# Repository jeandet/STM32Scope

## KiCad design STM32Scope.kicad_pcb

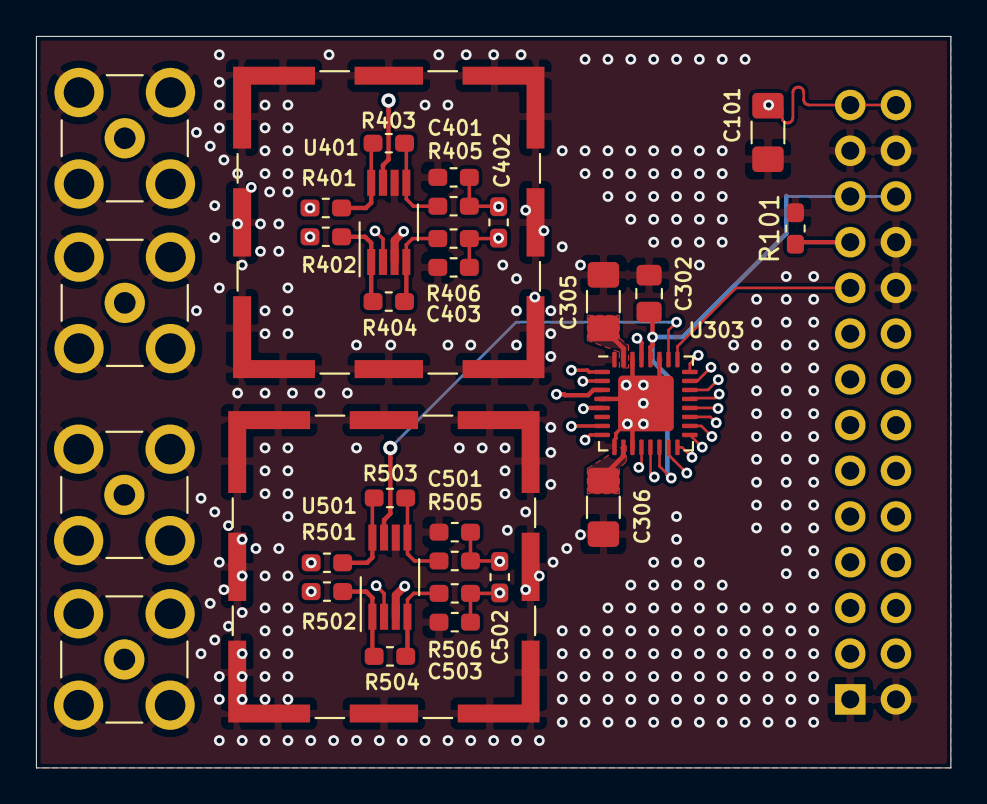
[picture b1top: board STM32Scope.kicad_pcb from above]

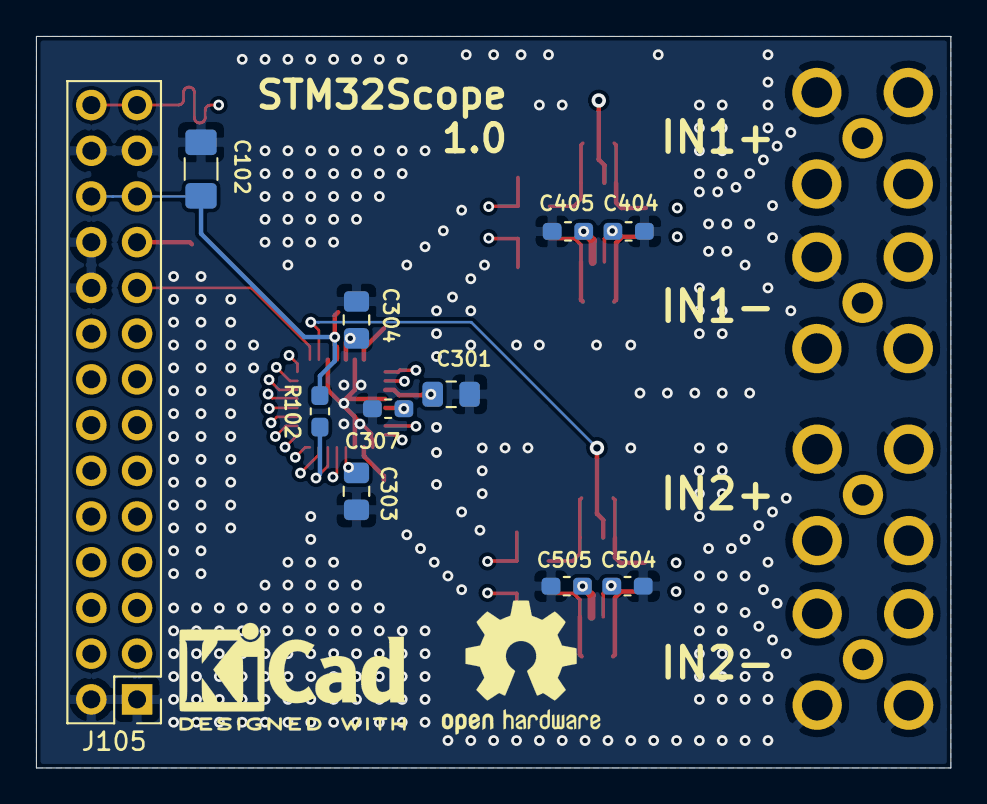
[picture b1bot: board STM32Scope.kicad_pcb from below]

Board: 4 copper layers, 50.8 x 40.6 mm, 45 parts (13 on the bottom side), 37 nets.

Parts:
C101, C102, C305, C306: 10µF; C_1206_3216Metric_Pad1.42x1.75mm_HandSolder
C301, C302, C303, C304: 1µF; C_0805_2012Metric_Pad1.15x1.40mm_HandSolder
C307: 10µF; C_0603_1608Metric_Pad1.05x0.95mm_HandSolder
C401, C403, C501, C503: 330pF; C_0603_1608Metric_Pad1.05x0.95mm_HandSolder
C402, C502: 3300pF; C_0603_1608Metric_Pad1.05x0.95mm_HandSolder
C404, C504: 100nF; C_0603_1608Metric_Pad1.05x0.95mm_HandSolder
C405, C505: 100nF; R_0603_1608Metric_Pad1.05x0.95mm_HandSolder
H101, H102: MountingHole_Pad; Laird_Technologies_BMI-S-102_16.50x16.50mm
J101, J102, J103, J104: Conn_Coaxial; SMB_Jack_Vertical
J105: Conn_02x14_Odd_Even; PinHeader_2x14_P2.54mm_Vertical
LOGO101: Logo_Open_Hardware_Large; OSHW-Logo2_9.8x8mm_SilkScreen
LOGO102: Logo_Open_Hardware_Small; KiCad-Logo2_5mm_SilkScreen
R101, R102: 100k; R_0603_1608Metric_Pad1.05x0.95mm_HandSolder
R401, R402, R403, R404, R501, R502, R503, R504: 1000; R_0603_1608Metric_Pad1.05x0.95mm_HandSolder
R405, R406, R505, R506: 40; R_0603_1608Metric_Pad1.05x0.95mm_HandSolder
U303: ADS92x4R; VQFN-32-1EP_5x5mm_P0.5mm_EP3.1x3.1mm
U401, U501: THS4551; VSSOP-8_3.0x3.0mm_P0.65mm

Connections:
/AVDD: C101.1, C303.2, C304.2, C405.1, C505.1, J105.27, J105.28, U303.12, U303.29, U401.3, U501.3
/CONVST: J105.8, U303.13
/DVDD: C102.1, C302.2, J105.23, J105.24, R102.1, U303.28
/READY_STROBE: J105.19, U303.25
/SCLK: J105.9, U303.16
/SDI: J105.10, U303.15
/SDO-0_0A: J105.17, U303.24
/SDO-1_1A: J105.18, U303.23
/SDO-2_2A: J105.15, U303.22
/SDO-3_3A: J105.16, U303.21
/SDO-4_0B: J105.13, U303.20
/SDO-5_1B: J105.14, U303.19
/SDO-6_2B: J105.11, U303.18
/SDO-7_3B: J105.12, U303.17
/Sheet5F0606FF/IN1M: J102.1, R402.2
/Sheet5F0606FF/IN1P: J101.1, R401.2
/Sheet5F0606FF/IN2M: J104.1, R502.2
/Sheet5F0606FF/IN2P: J103.1, R501.2
/Sheet5F0606FF/REFby2: C301.1, C404.1, C504.1, U303.3, U401.2, U501.2
/Sheet5F0606FF/Sheet5F0B5C34/OUTM: C401.2, C402.1, R405.1, U303.2
/Sheet5F0606FF/Sheet5F0B5C34/OUTP: C402.2, C403.1, R406.1, U303.1
/Sheet5F0606FF/sheet5F0E9B95/OUTM: C501.2, C502.1, R505.1, U303.7
/Sheet5F0606FF/sheet5F0E9B95/OUTP: C502.2, C503.1, R506.1, U303.8
/~CS: J105.7, R102.2, U303.14
/~POWERDOWN: J105.21, R101.1, U303.26, U401.7, U501.7
GND: C101.2, C102.2, C301.2, C302.1, C303.1, C304.1, C305.1, C306.2, C307.1, C401.1, C403.2, C404.2, C405.2, C501.1, C503.2, C504.2, C505.2, H101.1, H102.1, J101.2, J102.2, J103.2, J104.2, J105.1, J105.2, J105.20, J105.22, J105.25, J105.26, R101.2, U303.4, U303.9, U303.11, U303.27, U303.30, U303.32, U303.33, U401.6, U501.6
unnamed: C305.2, U303.31
unnamed: C306.1, U303.10
unnamed: C307.2, U303.5
unnamed: R401.1, R403.2, U401.8
unnamed: R402.1, R404.2, U401.1
unnamed: R403.1, R405.2, U401.5
unnamed: R404.1, R406.2, U401.4
unnamed: R501.1, R503.2, U501.8
unnamed: R502.1, R504.2, U501.1
unnamed: R503.1, R505.2, U501.5
unnamed: R504.1, R506.2, U501.4

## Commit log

2020-07-07 First init, ready for review
2020-07-07 Mirrored inputs labels on bottom silk screen
2020-07-08 Added pull resistors to deselect and powerdown by defalut all ICs and more GND vias!
2020-07-08 Few cleanups
2020-07-08 Ready for manufacturing v1.0
